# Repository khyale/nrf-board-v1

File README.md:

# nrf-board-v1
Projeto PCB de módulo transceptor digital de 2.4GHz Nordic NRF24L01P

Projeto de placa de circuito impresso de tranceptor digital operando 
na faixa de 2,4GHz, baseado no chip da Nordic Semiconductor, NRF24L01P.
A placa possui conector de barras de pinos (2x4) para conexão com uC 
através dos sinais CSN, MOSI, MISO, SCK (interface SPI), /IRQ (interrupção)
, alem do VDD e GND.

Utilizou-se um conector SMA horizontal para conexão com a antena 
dipolo de 2,4GHz.

O circuito não foi projetado com regulador de tensão, com o objetivo de reduzir
custo e manter o baixo consumo de energia, sendo ideal para aplicações utilizem baterias.

A  princípio, o módulo pode ser alimentado com tensões de 1.9 a 3.6V (2 a 3 pilhas de NiMH)
A corrente de standby é de apenas 26uA.

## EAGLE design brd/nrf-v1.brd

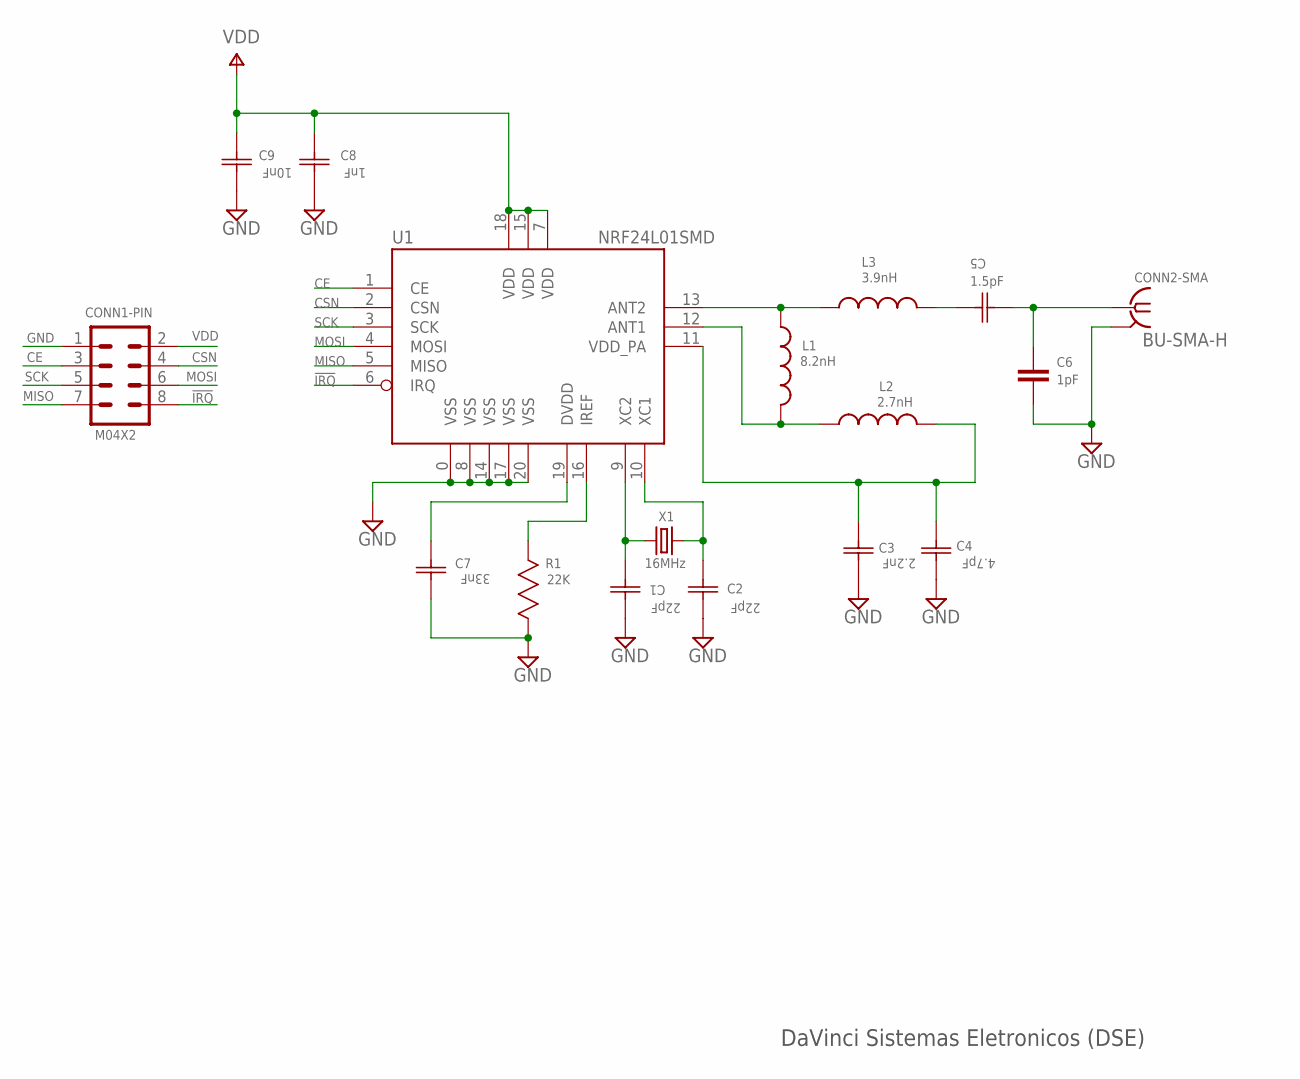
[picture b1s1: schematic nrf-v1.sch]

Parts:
C1, C2: 22pF; CAPC1005X60N
C3: 2.2nF; CAPC1005X60N
C4: 4.7pF; CAPC1005X60N
C5: 1.5pF; CAPC1005X60N
C6: 1pF; C01005
C7: 33nF; CAPC1005X60N
C8: 1nF; CAPC1005X60N
C9: 10nF; CAPC1005X60N
CONN1-PIN: M04X2; 2X4
CONN2-SMA: BU-SMA-H
L1: 8.2nH; C0402
L2: 2.7nH; C0402
L3: 3.9nH; C0402
R1: 22K; RESC1005X40N
U1: NRF24L01SMD; QFN20
X1: 16MHz; CRYSTAL-TXC-7A

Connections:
!IRQ: CONN1-PIN.8, U1.6 (IRQ)
CE: CONN1-PIN.3, U1.1 (CE)
CSN: CONN1-PIN.4, U1.2 (CSN)
GND: C1.2 (C1), C2.2 (C1), C3.2 (C1), C4.2 (C1), C6.2, C7.2 (C1), C8.2 (C1), C9.2 (C1), CONN1-PIN.1, CONN2-SMA.2, CONN2-SMA.3 (2), CONN2-SMA.4 (2), CONN2-SMA.5 (2), R1.1, U1.0 (VSS), U1.8 (VSS), U1.14 (VSS), U1.17 (VSS), U1.20 (VSS)
MISO: CONN1-PIN.7, U1.5 (MISO)
MOSI: CONN1-PIN.6, U1.4 (MOSI)
unnamed: C1.1 (C2), U1.9 (XC2), X1.P$1 (1)
unnamed: C2.1 (C2), U1.10 (XC1), X1.P$2 (2)
unnamed: L1.1, L3.1, U1.13 (ANT2)
unnamed: C5.1 (C2), L3.2
unnamed: C5.2 (C1), C6.1, CONN2-SMA.1
unnamed: L1.2, L2.1, U1.12 (ANT1)
unnamed: C3.1 (C2), C4.1 (C2), L2.2, U1.11 (VDD_PA)
unnamed: C7.1 (C2), U1.19 (DVDD)
unnamed: R1.2, U1.16 (IREF)
SCK: CONN1-PIN.5, U1.3 (SCK)
VDD: C8.1 (C2), C9.1 (C2), CONN1-PIN.2, U1.7 (VDD), U1.15 (VDD), U1.18 (VDD)

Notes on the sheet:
DaVinci Sistemas Eletronicos (DSE)

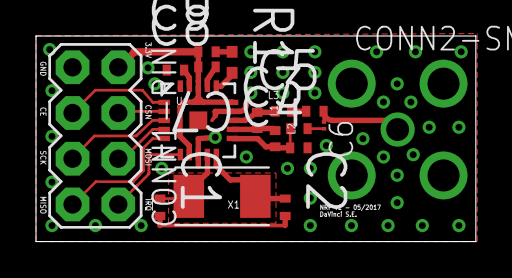
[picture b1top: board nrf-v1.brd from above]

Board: 2 copper layers, 24.4 x 11.4 mm, 17 parts (0 on the bottom side), 17 nets.

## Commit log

2017-05-08 adicionado a BOM
2017-05-08 deletado a bom
2017-05-08 arquivos adicionados
2017-05-08 Readme atualizado

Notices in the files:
parts and their libraries:
SparkFun-RF: Licensing: CC v3.0 Share-Alike You are welcome to use this library for commercial purposes.
